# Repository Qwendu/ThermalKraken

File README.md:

# Thermal Kraken
Measure Temperature at many locations with high 
bandwidth.

## Requirements

### 
16 Thermo Couple Leads
1kHz Bandwidth

### Data Extraction
SD Card storage
CSV format

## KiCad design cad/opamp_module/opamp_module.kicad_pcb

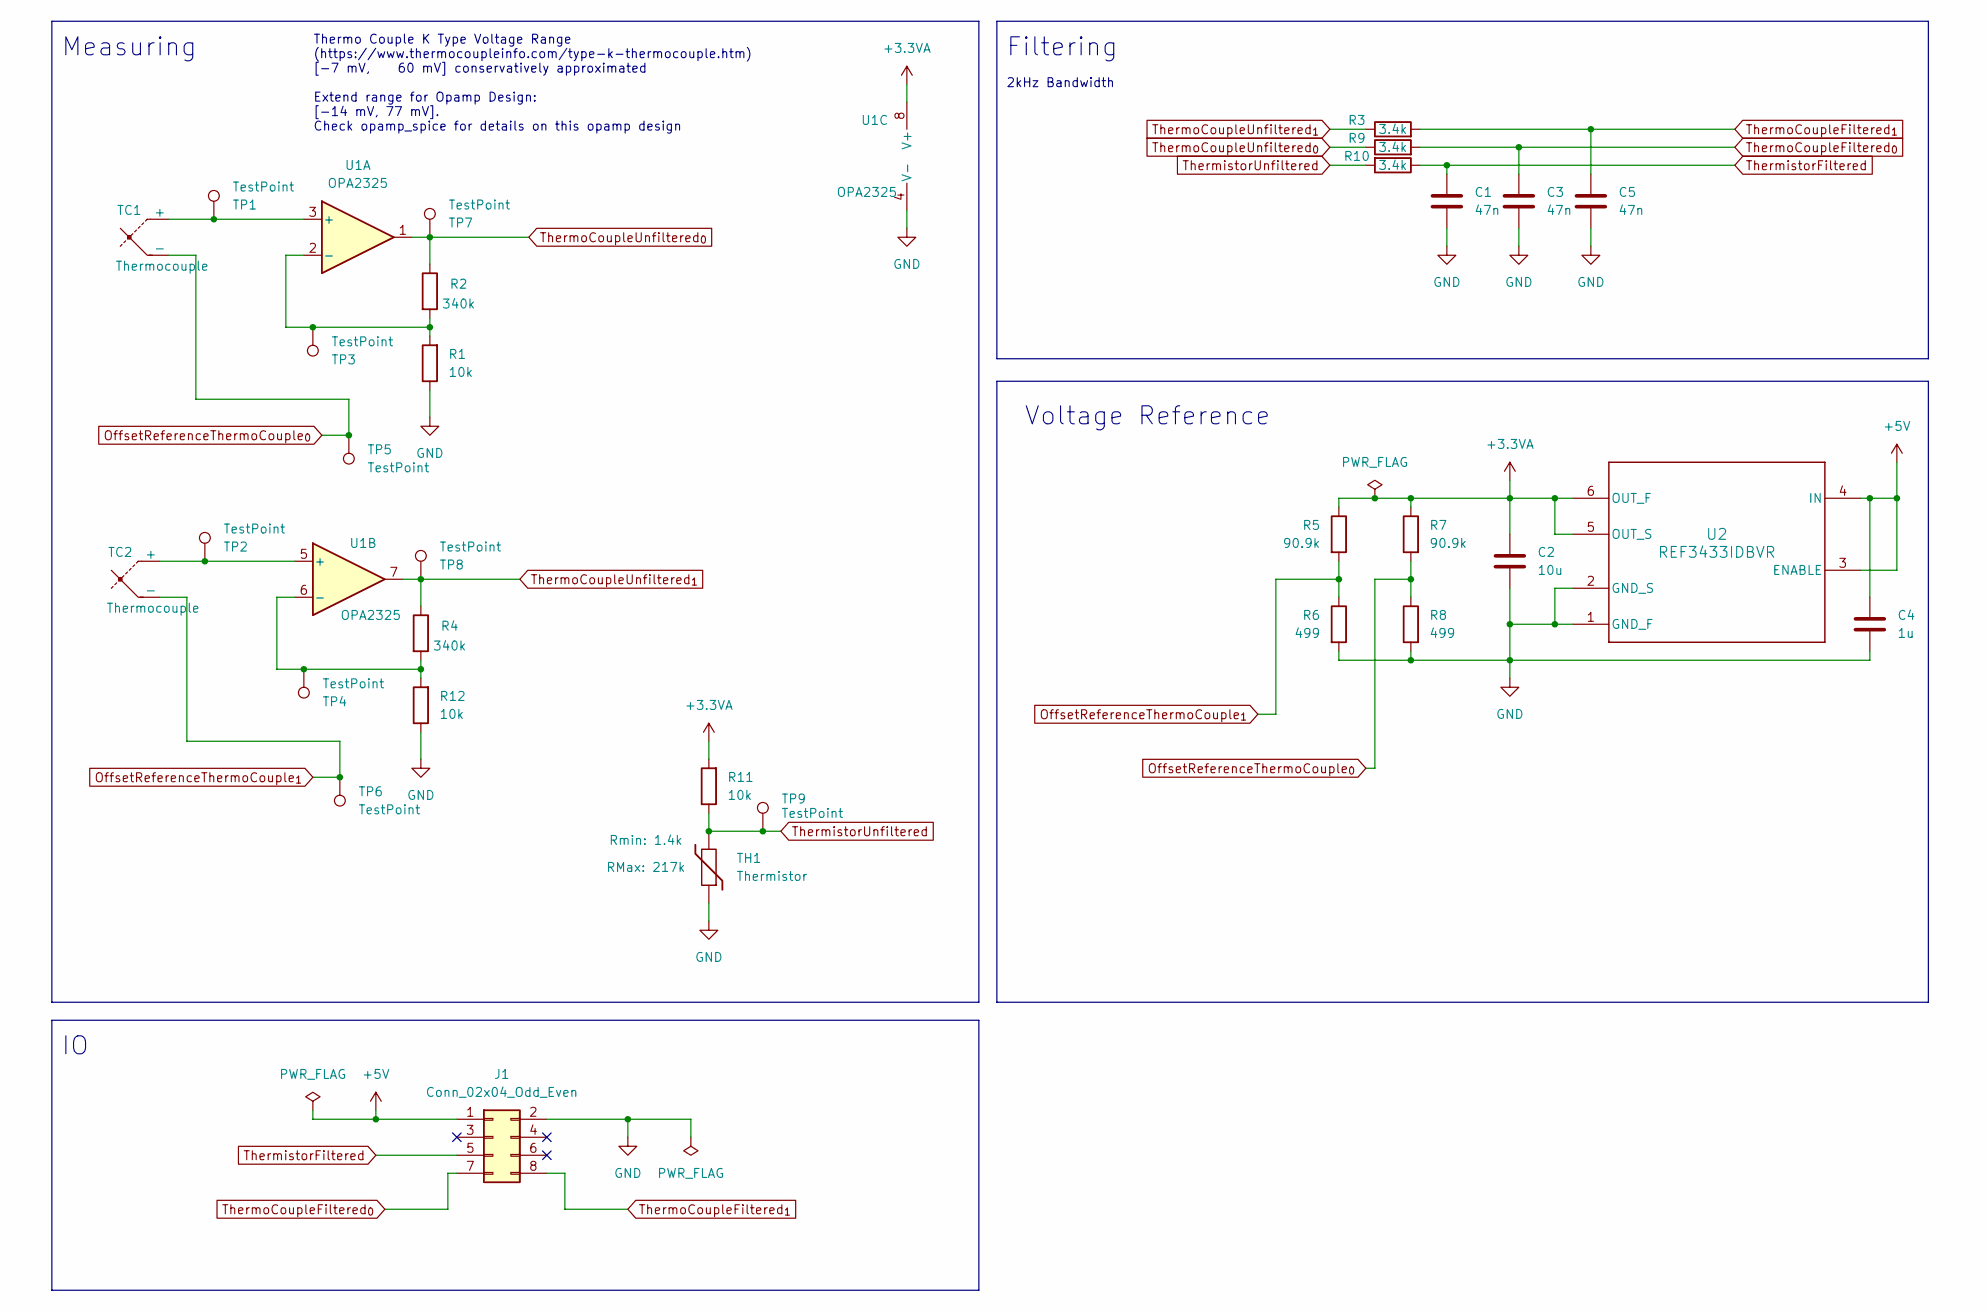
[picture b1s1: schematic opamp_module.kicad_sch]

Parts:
C1, C3, C5: 47n; C_0805_2012Metric_Pad1.18x1.45mm_HandSolder
C2: 10u; C_0805_2012Metric_Pad1.18x1.45mm_HandSolder
C4: 1u; C_0805_2012Metric_Pad1.18x1.45mm_HandSolder
J1: Conn_02x04_Odd_Even; PinHeader_2x04_P2.54mm_Vertical
R1, R11, R12: 10k; R_0805_2012Metric_Pad1.20x1.40mm_HandSolder
R2, R4: 340k; R_0805_2012Metric_Pad1.20x1.40mm_HandSolder
R3, R9, R10: 3.4k; R_0805_2012Metric_Pad1.20x1.40mm_HandSolder
R5, R7: 90.9k; R_0805_2012Metric_Pad1.20x1.40mm_HandSolder
R6, R8: 499; R_0805_2012Metric_Pad1.20x1.40mm_HandSolder
TC1, TC2: Thermocouple; PinHeader_1x02_P2.54mm_Vertical
TH1: Thermistor; R_0805_2012Metric_Pad1.20x1.40mm_HandSolder
TP1, TP2, TP3, TP4, TP5, TP6, TP7, TP8, TP9: TestPoint; TestPoint_Pad_D2.0mm
U1: OPA2325; SOIC-8_3.9x4.9mm_P1.27mm
U2: REF3433IDBVR; DBV0006A_N

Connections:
+3.3VA: C2.1, R5.1, R7.1, R11.2, U1.8 (V+), U2.5 (OUT_S), U2.6 (OUT_F)
+5V: C4.1, J1.1, U2.3 (ENABLE), U2.4 (IN)
GND: C1.2, C2.2, C3.2, C4.2, C5.2, J1.2, R1.1, R6.2, R8.2, R12.1, TH1.1, U1.4 (V-), U2.1 (GND_F), U2.2 (GND_S)
unnamed: TC1.1 (+), TP1.1, U1.3 (+)
unnamed: TC2.1 (+), TP2.1, U1.5 (+)
unnamed: R1.2, R2.2, TP3.1, U1.2 (-)
unnamed: R4.2, R12.2, TP4.1, U1.6 (-)
OffsetReferenceThermoCouple_{0}: R7.2, R8.1, TC1.2 (-), TP5.1
OffsetReferenceThermoCouple_{1}: R5.2, R6.1, TC2.2 (-), TP6.1
ThermistorFiltered: C1.1, J1.5, R10.1
ThermistorUnfiltered: R10.2, R11.1, TH1.2, TP9.1
ThermoCoupleFiltered_{0}: C3.1, J1.7, R9.2
ThermoCoupleFiltered_{1}: C5.1, J1.8, R3.2
ThermoCoupleUnfiltered_{0}: R2.1, R9.1, TP7.1, U1.1
ThermoCoupleUnfiltered_{1}: R3.1, R4.1, TP8.1, U1.7

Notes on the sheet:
2kHz Bandwidth
Filtering
Measuring
Thermo Couple K Type Voltage Range (https://www.thermocoupleinfo.com/type-k-thermocouple.htm) [-7 mV, 60 mV] conservatively approximated Extend range for Opamp Design: [-14 mV, 77 mV]. Check opamp_spice for details on this opamp design
Voltage Reference

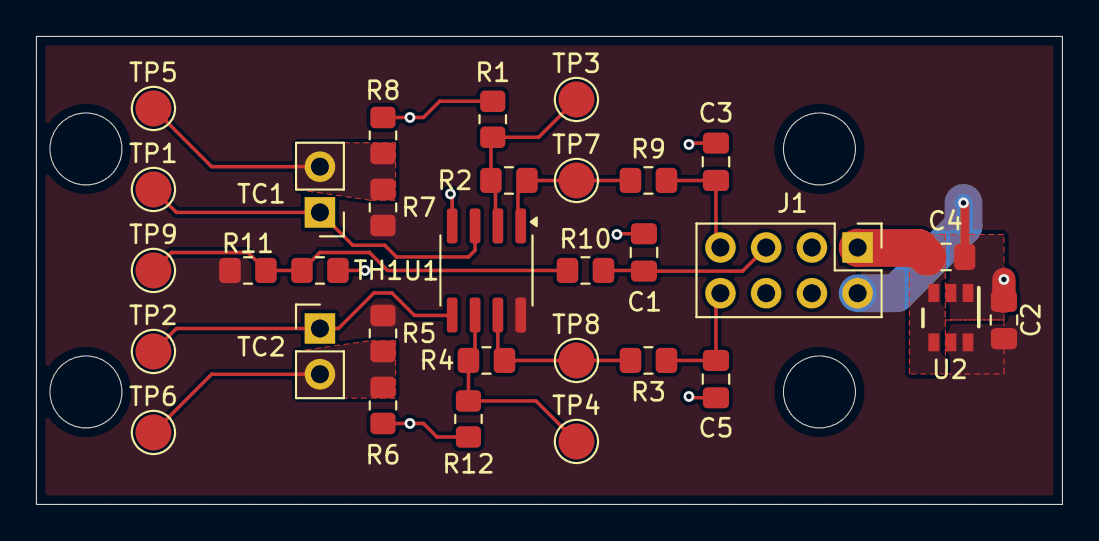
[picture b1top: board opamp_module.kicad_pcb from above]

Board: 2 copper layers, 57.0 x 26.0 mm, 32 parts (0 on the bottom side), 15 nets.

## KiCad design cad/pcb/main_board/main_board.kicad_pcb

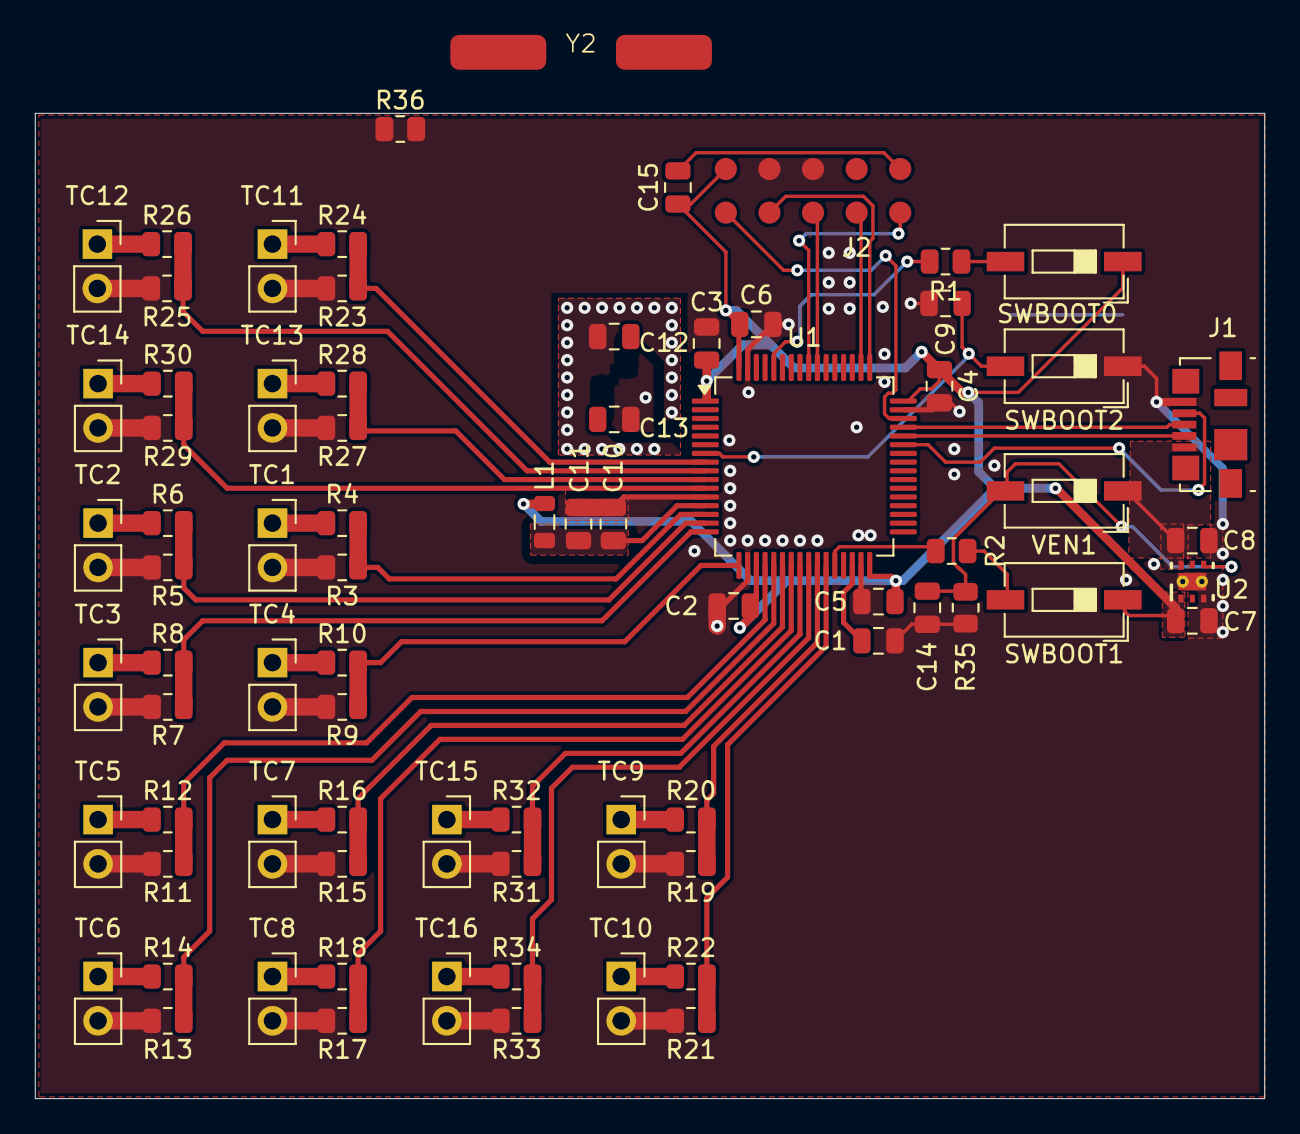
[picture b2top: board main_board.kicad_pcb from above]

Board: 2 copper layers, 70.5 x 56.5 mm, 77 parts (0 on the bottom side), 55 nets.

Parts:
C1: 2u2F; C_0805_2012Metric
C2: 4u7F; C_0805_2012Metric
C3, C4, C5, C6, C11: 100nF; C_0805_2012Metric
C7, C8, C10: 1uF; C_0805_2012Metric
C9, C14: 0u1F; C_0805_2012Metric
C12: CL1; C_0805_2012Metric
C13: CL2; C_0805_2012Metric
C15: C; C_0805_2012Metric
J1: USB_B_Micro; USB_Micro-B_Molex_47346-0001
J2: Conn_ARM_JTAG_SWD_10; POGO_JTAG_SWD
L1: L; L_0805_2012Metric
R1, R2, R3, R4, R5, R6, R7, R8, R9, R10, R11, R12, R13, R14, R15, R16, R17, R18, R19, R20, R21, R22, R23, R24, R25, R26, R27, R28, R29, R30, R31, R32, R33, R34: 10kR; R_0805_2012Metric
R35: 10k; R_0805_2012Metric
R36: 1421R; R_0805_2012Metric
SWBOOT0, SWBOOT1, SWBOOT2: SW_DIP_x01; SW_DIP_SPSTx01_Slide_6.7x4.1mm_W6.73mm_P2.54mm_LowProfile_J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
TC1, TC2, TC3, TC4, TC5, TC6, TC7, TC8, TC9, TC10, TC11, TC12, TC13, TC14, TC15, TC16: 0-60V; PinSocket_1x02_P2.54mm_Vertical
U1: STM32F401R_B-C_Tx; LQFP-64_10x10mm_P0.5mm
U2: TLV75533PDRVR; DRV0006A
VEN1: SW_DIP_x01; SW_DIP_SPSTx01_Slide_6.7x4.1mm_W6.73mm_P2.54mm_LowProfile_J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
Y2: 8MHz, CL=12p; FC4SDCBMF8.0-T1

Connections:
/MCU/ADC_IN0: R3.1, R4.2, U1.14 (ADC1_IN0)
/MCU/ADC_IN1: R5.1, R6.2, U1.15 (ADC1_IN1)
/MCU/ADC_IN2: R7.1, R8.2, U1.16 (ADC1_IN2)
/MCU/ADC_IN3: R9.1, R10.2, U1.17 (ADC1_IN3)
/MCU/ADC_IN4: R11.1, R12.2, U1.20 (ADC1_IN4)
/MCU/ADC_IN5: R13.1, R14.2, U1.21 (ADC1_IN5)
/MCU/ADC_IN6: R15.1, R16.2, U1.22 (ADC1_IN6)
/MCU/ADC_IN7: R17.1, R18.2, U1.23 (ADC1_IN7)
/MCU/ADC_IN8: R19.1, R20.2, U1.26 (ADC1_IN8)
/MCU/ADC_IN9: R21.1, R22.2, U1.27 (ADC1_IN9)
/MCU/ADC_IN10: R23.1, R24.2, U1.8 (ADC1_IN10)
/MCU/ADC_IN11: R25.1, R26.2, U1.9 (ADC1_IN11)
/MCU/ADC_IN12: R27.1, R28.2, U1.10 (ADC1_IN12)
/MCU/ADC_IN13: R29.1, R30.2, U1.11 (ADC1_IN13)
/MCU/ADC_IN14: R31.1, R32.2, U1.24 (ADC1_IN14)
/MCU/ADC_IN15: R33.1, R34.2, U1.25 (ADC1_IN15)
/MCU/USB_D+: J1.3 (D+), U1.45 (USB_D+)
/MCU/USB_D-: J1.2 (D-), U1.44 (USB_D-)
/MCU/USB_ID: J1.4 (ID), U1.43 (USB_ID)
BOOT0: R1.2, U1.60 (BOOT0)
BOOT1: R2.2, U1.28 (PB2)
unnamed: C13.1, R36.2, Y2.2
unnamed: C15.2, J2.9 (GNDDetect)
unnamed: J2.8 (NC/TDI), U1.50 (SYS_JTDI)
unnamed: J2.4 (SWCLK/TCK), U1.49 (SYS_JTCK-SWCLK)
unnamed: J2.2 (SWDIO/TMS), U1.46 (SYS_JTMS-SWDIO)
unnamed: J2.6 (SWO/TDO), U1.55 (SYS_JTDO-SWO)
unnamed: J2.10 (~RESET), U1.56 (SYS_JTRST)
unnamed: R1.1, SWBOOT0.2
unnamed: R2.1, SWBOOT1.2
unnamed: R4.1, TC1.1 (+)
unnamed: R6.1, TC2.1 (+)
unnamed: R8.1, TC3.1 (+)
unnamed: R10.1, TC4.1 (+)
unnamed: R12.1, TC5.1 (+)
unnamed: R14.1, TC6.1 (+)
unnamed: R16.1, TC7.1 (+)
unnamed: R18.1, TC8.1 (+)
unnamed: R20.1, TC9.1 (+)
unnamed: R22.1, TC10.1 (+)
unnamed: R24.1, TC11.1 (+)
unnamed: R26.1, TC12.1 (+)
unnamed: R28.1, TC13.1 (+)
unnamed: R30.1, TC14.1 (+)
unnamed: R32.1, TC15.1 (+)
unnamed: R34.1, TC16.1 (+)
unnamed: C9.2, SWBOOT2.2, U1.7 (NRST)
unnamed: C12.1, U1.5 (OSC_IN), Y2.1
unnamed: R36.1, U1.6 (OSC_OUT)
unnamed: C1.1, U1.30 (VCAP1)
unnamed: C14.1, R35.1, U2.4 (EN), VEN1.2
VBUS: C8.2, J1.1 (VBUS), U2.6 (IN), VEN1.1
VDD: C2.1, C3.1, C4.1, C5.1, C6.1, C7.1, C15.1, J2.1 (VTref), L1.1, SWBOOT0.1, SWBOOT1.1, U1.1 (VBAT), U1.19 (VDD), U1.32 (VDD), U1.48 (VDD), U1.64 (VDD), U2.1 (OUT)
VDDA: C10.1, C11.1, L1.2, U1.13 (VREF+)
VSS: C1.2, C2.2, C3.2, C4.2, C5.2, C6.2, C7.2, C8.1, C9.1, C10.2, C11.2, C12.2, C13.2, C14.2, J1.5 (GND), J2.3 (GND), J2.5 (GND), R3.2, R5.2, R7.2, R9.2, R11.2, R13.2, R15.2, R17.2, R19.2, R21.2, R23.2, R25.2, R27.2, R29.2, R31.2, R33.2, R35.2, SWBOOT2.1, TC1.2 (-), TC2.2 (-), TC3.2 (-), TC4.2 (-), TC5.2 (-), TC6.2 (-), TC7.2 (-), TC8.2 (-), TC9.2 (-), TC10.2 (-), TC11.2 (-), TC12.2 (-), TC13.2 (-), TC14.2 (-), TC15.2 (-), TC16.2 (-), U1.12 (VSSA), U1.18 (VSS), U1.31 (VSS), U1.47 (VSS), U1.63 (VSS), U2.3 (GND), U2.7 (PAD)

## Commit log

2024-08-21 Adding README
2024-08-22 Kicad project
2024-08-22 Plugins
2024-08-22 recreate project
2024-08-22 PowerSupply
2024-08-22 VDDA, BOOT SEL
2024-08-22 HSE, usb, TC
2024-08-22 Thermo Couple Pins
2024-09-19 Adding Voltage Regulators, Adding SD Card Symbol
2024-09-19 Add usb an/ add missing connections note
2024-09-19 Add Aisler files
2024-09-19 Upgrading to kicad 8.0, adding aisler drc
2024-09-19 First Layout of Voltage Regulator, Status LED note, add pulldown resistor for Voltage Regulator Enable
2024-09-19 Tighter Layout for USB Micro and Power Delivery. Worse design for ADC routing on left side of MCU.
    Revise revise revise
2024-09-19 Some more routing
2024-09-20 Add Checklist for various Stages
2024-09-20 Organizing Thermo Couple Connections
2024-09-20 Aligning Thermo Couple Resistors
2024-09-20 Hooking up ThermoCouple pins first layout of TCs
2024-09-21 Adding JTAG Interface + POGO Pads
2024-09-21 Updating Checklist
2024-09-21 Add .gitignore to ignore lock files
2024-09-21 Remove rounded version
2024-09-21 Redo Power And JTAG layout
2024-09-21 More bunching together, some jtag, voltage regulator layout
2024-09-21 Checking VBAT
2024-09-21 Oscillator Selection an and Layouting
2024-09-21 Update Checklist
2024-09-21 Connecting NRST, placing VSS Vias next to MCU Pins
2024-09-21 Power SUpply Struggles
2024-09-21 DRC mostly checks out now
2024-09-21 little wire shoving
2024-09-21 Split Copper Zones Front/Back so that openEMS FreeCAD import tool recognizes them
2024-09-22 Adding FEA simulation
2024-09-22 Redoing entire pcb
2024-09-22 Replace Push button with switch
2024-09-22 It looks messy
2024-09-22 Still looks messy
2024-09-22 Most DRC rules pass
2024-09-22 Restarting FEA, updating Checklist
2024-09-22 FEA dont work : (
2024-11-26 SWD connector start
2024-11-26 housekeeping
2024-11-27 Correct gain
2024-11-29 removing backups
2024-11-29 Calculating Turn off time, Looking up dropout voltage
2024-11-29 Add EmbeddedSys email todo and reverse voltage protection todo
2025-01-23 Start design of OPAMP module
2025-01-23 Add missing notes
2025-02-02 opamp module design
2025-02-02 low pass filter
2025-02-04 Spice based resistor selection :)
2025-02-04 layout
2025-02-05 Spice simulations and switching to two TC's per module
2025-02-06 Ordered
2025-02-10 Opamp as in order
